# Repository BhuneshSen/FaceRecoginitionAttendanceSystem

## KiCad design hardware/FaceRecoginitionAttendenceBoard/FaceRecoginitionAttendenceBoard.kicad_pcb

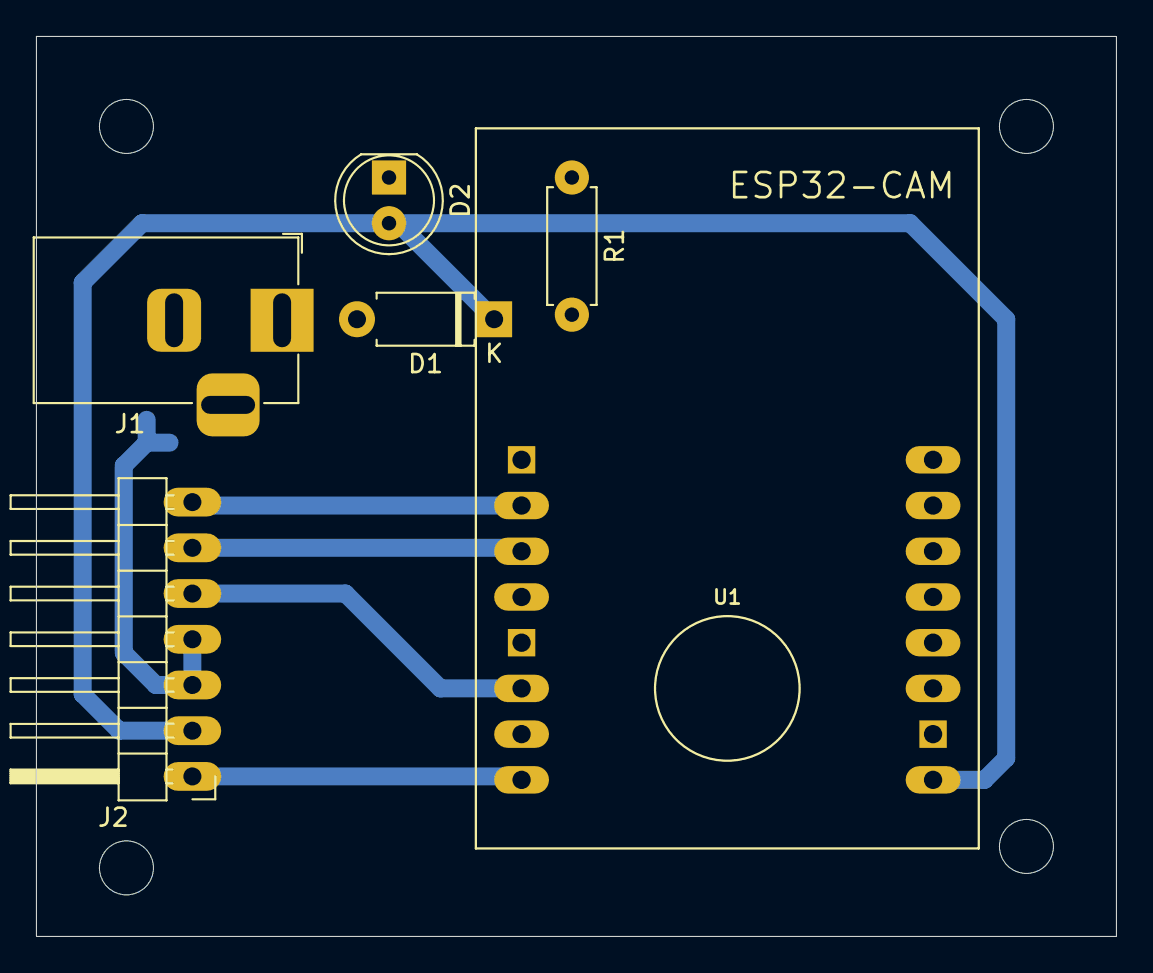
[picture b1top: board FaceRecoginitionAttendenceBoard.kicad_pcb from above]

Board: 2 copper layers, 60.0 x 50.0 mm, 6 parts (0 on the bottom side), 8 nets.

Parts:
D1: D; D_A-405_P7.62mm_Horizontal
D2: LED; LED_D5.0mm
J1: Barrel_Jack_Switch; BarrelJack_Horizontal
J2: PROGRAMMING CONNECTOR; PinHeader_1x07_P2.54mm_Horizontal
R1: 220R; R_Axial_DIN0207_L6.3mm_D2.5mm_P7.62mm_Horizontal
U1: ESP32-CAM

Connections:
+3.3V: J2.1, U1.P$8 (3V3)
+5V: D1.1 (K), D2.2 (A), J2.2, U1.P$9 (5V)
GND: J1.2, J1.3, J2.3, J2.4, R1.2, U1.P$1 (GND@1), U1.P$5 (GND@2), U1.P$10 (GND@3)
GPIO_0: J2.5, U1.P$6 (GPIO0)
unnamed: D1.2 (A), J1.1
unnamed: D2.1 (K), R1.1
UART_RX: J2.6, U1.P$3 (GPIO3)
UART_TX: J2.7, U1.P$2 (GPIO1)

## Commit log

2024-05-28 Added basic c file to test the functinality
2024-05-28 Designed PCB for the system in kiCAD v8
2024-05-28 Removed temperory C files, using to test the setup
2024-05-29 Updated hardware design
2024-05-29 Added source file
2024-05-29 I "ADDING PYTHON SOURCE FILE"
2024-05-29 updating src folder
2024-05-29 remove unwanted python source file, cleaned the repository
2024-05-29 Added gitIgnore and cleaned the hardware folder
